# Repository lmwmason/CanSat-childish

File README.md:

# CanSat-childish

CanSat-childish is the open-source code and hardware for a two-tier CanSat
project by the Space Chamchu team: a **mother CanSat** that is dropped, steadies
itself with a reaction wheel, spins up, opens a door, ejects its wings and
glides back around the drop point, and small **child CanSats** that fall under a
parachute and record the descent. A **ground station** receives the mother's
telemetry over a TBS Crossfire link, shows it live and records it to CSV.

The repository holds every part of the system:

- **Mother firmware** — STM32F410RB. Fuses two IMUs, detects the drop, stabilizes
  and spins the body with a reaction wheel, opens the door, ejects the wings,
  flies the elevons (manual from the radio or automatic with GPS), detects the
  landing, and sends telemetry down the CRSF link.
- **Child firmware** — ATmega328 (Arduino Pro Mini). Reads barometer, IMU and
  humidity sensors, releases a parachute with a servo and logs the whole flight
  to EEPROM so it can be dumped over serial after landing.
- **Ground station** — a PyQt6 desktop app (Mission Planner style) that runs on a
  Raspberry Pi with a Crossfire Micro TX V2, or on a normal PC. Live flight view,
  ground track, CSV recording and the AUX switches of the mother.
- **KAIST kit ground station** — a second, independent ground station for the
  official KAIST CanSat kit. It runs as a small local web server and shows the
  flight and the wind field in two browser windows side by side.
- **Simulator** — the flight logic as a hardware-independent C core, run on a
  rigid-body physics engine, with a live 3D viewer.
- **PCB** — the KiCad project of the mother board.

## Mother mission

The mother's mission is a state machine on the STM32. Every number below is a
constant in the source and can be tuned.

1. **Drop detection** — the acceleration magnitude stays between 9.7 and
   9.9 m/s² for 300 ms **and** the AUX1 switch on the radio is on.
2. **2 s later** — the reaction wheel turns on and holds the current heading.
3. **Stable** (yaw rate under 8°/s and yaw error under 10° for 1 s) — the wheel
   spins the body up at full power.
4. **180°/s reached** — the servo opens the door.
5. **5 s at maximum speed**, then the wheel brakes and holds the heading again.
6. **Stable again** — the two wing servos eject the wings.
7. **Elevons** — the AUX2 switch selects manual (sticks) or automatic. Automatic
   mode levels the aircraft and circles around the point where the drop was
   detected (50 m radius) using the GPS.
8. **Landing** — motionless for 3 s (at least 10 s after the drop): the buzzer
   sounds and all LEDs blink.

## Tech stack

- **Mother firmware:** C, STM32 HAL, [STM32CubeMX](https://www.st.com/en/development-tools/stm32cubemx.html) project (`.ioc`) with IAR EWARM project files
- **Sensors on the mother:** MPU6050 + ICM-42688 (I2C), u-blox NEO-6M GPS (I2C / DDC), TBS Crossfire receiver (CRSF, UART)
- **Child firmware:** C++ / Arduino framework with [PlatformIO](https://platformio.org/); BMP280, MPU6050 (on-chip DMP), DHT11
- **Ground station:** Python 3, [PyQt6](https://www.riverbankcomputing.com/software/pyqt/) (Qt Serial Port), [PyInstaller](https://pyinstaller.org/) and AppImage for releases
- **KAIST kit ground station:** Python 3 (standard-library HTTP server, numpy, Pillow, pyserial), a plain HTML / canvas browser UI; `wind_field/` for the wind estimate
- **Simulator:** C11, [Open Dynamics Engine](https://www.ode.org/), Python with matplotlib / numpy for the viewer
- **Hardware design:** [KiCad](https://www.kicad.org/)

## Getting started

### Ground station

The easiest way is a build from the
[Releases](https://github.com/lmwmason/CanSat-childish/releases) page:

| File | For |
| ---- | --- |
| `CanSatGroundStation-aarch64.AppImage` | Raspberry Pi 4 / 5, 64-bit OS |
| `CanSatGroundStation-x86_64.AppImage` | Linux PC |
| `CanSatGroundStation-…-windows-x64.zip` | Windows PC |
| `CanSatGroundStation.pyz` + `run-on-pi.sh` | Any Raspberry Pi OS, if the AppImage does not work |

On a Raspberry Pi:

```bash
sudo apt install libfuse2 libxcb-cursor0
chmod +x CanSatGroundStation-aarch64.AppImage
./CanSatGroundStation-aarch64.AppImage
```

To run it from source:

```bash
cd guiTool
python3 -m venv .venv
.venv/bin/pip install -r requirements.txt
.venv/bin/python -m cansat_gui
```

Pick **Demo (synthetic flight)** in the Mother bar to try everything without
hardware. For the real link, choose the serial port and 400000 baud (CRSF). The
wiring between the Raspberry Pi and the Crossfire module is in
[`guiTool/pinmap.md`](./guiTool/pinmap.md). Telemetry is recorded to
`~/CanSat Logs/` (or `guiTool/logs/` when run from source).

Run the tests with `python -m unittest discover -s tests` inside `guiTool`.
To build a release locally:

```bash
pip install -r requirements-build.txt
pyinstaller cansat_gui.spec --noconfirm
tools/make_appimage.sh
```

Pushing a tag named `gui-vX.Y.Z` makes GitHub Actions
([`gui-release.yml`](./.github/workflows/gui-release.yml)) build the AppImages
for aarch64 and x86_64 and the Windows zip, and publish them as a release.

### KAIST kit ground station

A separate program from the one above, for the official KAIST CanSat kit (GPS,
IMU, ATLM / DTLM channels, camera). It needs Python 3 with numpy, Pillow and
pyserial, and a browser.

```bash
python3 -m venv kaist_ground_station/.venv
kaist_ground_station/.venv/bin/pip install -r kaist_ground_station/requirements.txt
./kaist_ground_station/run.sh
```

`run.sh` finds the USB serial adapter, connects at 115200 baud, dials the kit's
Bluetooth address from the config and opens two windows: the flight and control
page at `http://127.0.0.1:8765/` and the wind-field page at `/wind`. If no
adapter is found the UI still opens so a port can be picked by hand.

| Command | What it does |
| ------- | ------------ |
| `run.sh` / `run.sh live [PORT]` | Connect to the kit |
| `run.sh demo` | Replay the bundled example recording, no hardware needed |
| `run.sh replay FILE` | Replay a recorded `traffic.jsonl` |
| `run.sh mock` | Fake kit built from a real GoPro descent, for trying the UI |
| `run.sh headless` | Capture without a window |
| `run.sh test` | Run the unit tests |

Nothing is recorded until **Record** is pressed (or `auto_start` is set).
Checkpoints such as *Drop* or *Parachute open* are saved with the recording and
shown again in a replay. Language, colors, fonts, alarm limits, checkpoint
buttons, the Bluetooth address and the windows to open are all in
[`kaist_ground_station/config/ui.cfg`](./kaist_ground_station/config/ui.cfg).
Protocol notes and the hardware test steps are in
[`kaist_ground_station/`](./kaist_ground_station/).

### Mother firmware

1. Open `firmware/motherCansat-Firmware/motherCansat-Firmware.ioc` in
   STM32CubeMX to inspect or regenerate the peripheral setup.
2. Build and flash with your STM32 toolchain (the `EWARM` folder contains the IAR
   project). Keep your own code inside the `USER CODE` blocks of `main.c`.
3. Check the wiring against
   [`firmware/motherCansat-Firmware/pinmap.md`](./firmware/motherCansat-Firmware/pinmap.md).
   Several pins (wheel motor, servos, buzzer, LEDs) are not labeled in the `.ioc`,
   so the pin map is the reference.

The mission constants live in the headers of the modules, for example
`mission.h`, `drop_detect.h`, `landing_detect.h`, `elevon.h` and `nav.h`.

### Child firmware

```bash
cd firmware/childCansat-Firmware
pio run -t upload
pio device monitor -b 115200
```

The serial monitor accepts `s` (status), `d` (dump the flight log as CSV) and
`e` (erase the log).

### Simulator

Needs `gcc`, `make`, the ODE development package (`ode-devel` on Fedora,
`libode-dev` on Debian / Ubuntu) and Python with `matplotlib` and `numpy` for the
viewer.

```bash
cd simulator
./run.sh              # build, then an interactive menu
./run.sh mother       # the mothership simulation
./run.sh child 1      # a child satellite simulation (1 to 3)
./run.sh test         # the headless failsafe test
./run.sh viz          # live 3D telemetry viewer
./run.sh all          # mother + 3 children + viewer together
```

## Project structure

```
firmware/
  childCansat-Firmware/    PlatformIO project of the child CanSat
    src/                   main, boot, mission, sensors, storage (EEPROM log), comm, ui, core, config
    lib/                   bmp280, dht11 and mpu6050 drivers
    pinmap.md              Pin assignments of the child
  motherCansat-Firmware/   STM32CubeMX project of the mother CanSat
    Core/Src/              main.c and the application modules:
                             imu, gps, nav, crsf, drop, mission, reaction_wheel, pid,
                             door, wings, elevon, soft_pwm, wheel_motor, landing, indicator
    pinmap.md              Pin assignments of the mother
guiTool/
  cansat_gui/              The PyQt6 ground station (CRSF decoder, CSV logger, pages)
  tests/                   Frame-format tests against the real firmware output
  tools/                   Packaging scripts (AppImage, .pyz, Raspberry Pi launcher)
  pinmap.md                Wiring Raspberry Pi <-> Crossfire TX module
kaist_ground_station/      Ground station for the KAIST kit (web UI)
  web/                     HTTP server and the browser page
  config/                  ui.cfg (language, colors, alarms, checkpoints)
  demo/                    Bundled example recording for `run.sh demo`
  tools/                   Mock kit for trying the UI without hardware
wind_field/                 Wind estimate from GPS descents, used by the KAIST ground station
simulator/
  core/                    Hardware-independent flight logic in C
  sim/                     Mothership and child simulations (physics)
  viz/                     Live 3D viewer (Python)
pcb/
  motherBoard/kicad-pcb/   KiCad project of the mother board
photos/                    Schematic and PCB exports
.github/workflows/         Ground station release build
```

## Status

The mother firmware and the ground station are verified on a PC: the telemetry
frames the firmware produces are decoded correctly by the ground station, and the
mission logic was simulated. They have **not yet been tested end to end on the
real hardware**. The mother's pin assignments are chosen in `pinmap.md`, and the
Crossfire module pins should be checked before powering anything.

The KAIST kit ground station has received and recorded real flights from the kit
over its Bluetooth link. The kit sends GPS, IMU and ATLM about every 2 seconds
because its single transmit queue is shared with the camera image.

## License

Licensed under the [Apache License 2.0](./LICENSE).

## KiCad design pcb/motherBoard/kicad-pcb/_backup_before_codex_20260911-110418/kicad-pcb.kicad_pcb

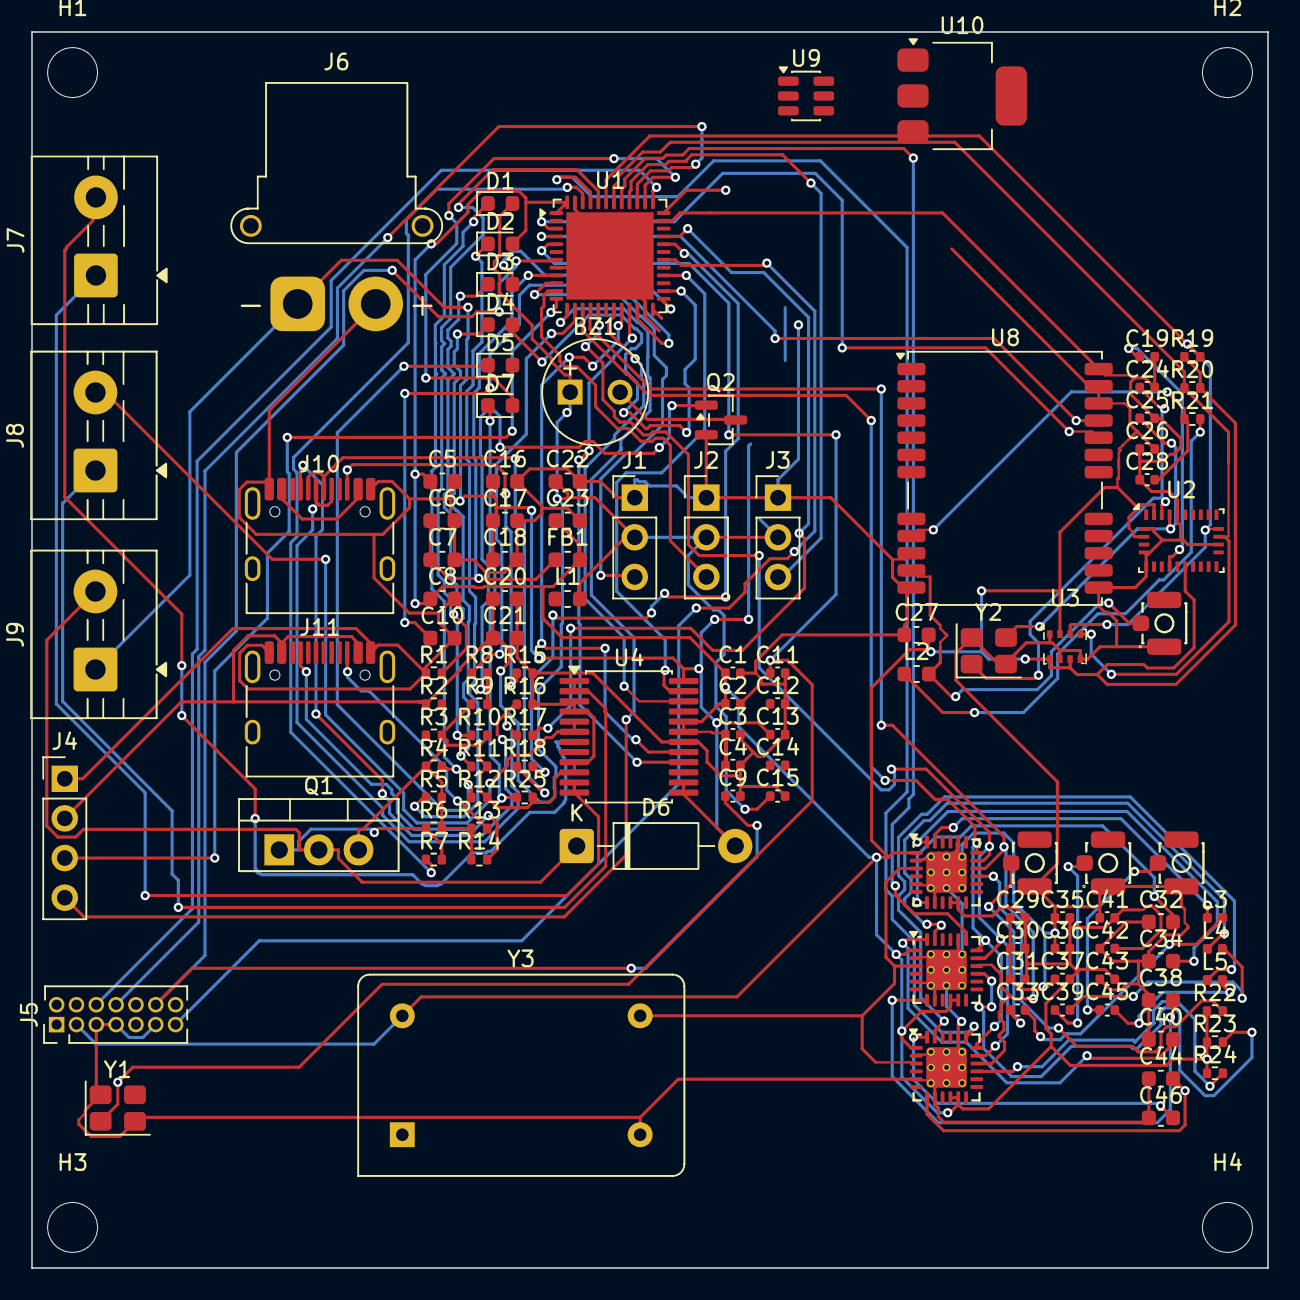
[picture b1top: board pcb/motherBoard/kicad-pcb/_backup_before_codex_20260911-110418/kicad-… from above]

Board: 2 copper layers, 79.2 x 79.2 mm, 119 parts (0 on the bottom side), 93 nets.

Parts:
BZ1: Buzzer; MagneticBuzzer_Kingstate_KCG0601
C1, C2, C3, C4, C9, C11, C12, C13, C14, C15, C19, C26, C29, C30, C31, C35, C36, C37, C41, C42, C43: 100n; C_0402_1005Metric
C5, C16, C17, C27: 10u; C_0603_1608Metric
C6: 10n; C_0603_1608Metric
C7, C8: 1u; C_0603_1608Metric
C10, C32, C34, C38, C40, C44, C46: 4.7u; C_0603_1608Metric
C18: 100u; C_0603_1608Metric
C20, C21, C22, C23: 22u; C_0603_1608Metric
C24, C25: 22p; C_0402_1005Metric
C28: 10n; C_0402_1005Metric
C33, C39, C45: 10p; C_0402_1005Metric
D1, D2: RED; LED_0603_1608Metric
D3: BLUE; LED_0603_1608Metric
D4: YELLOW; LED_0603_1608Metric
D5: ORANGE; LED_0603_1608Metric
D6: 1N4007; D_DO-41_SOD81_P10.16mm_Horizontal
D7: PINK; LED_0603_1608Metric
FB1: 120R; L_0603_1608Metric
H1, H2, H3, H4: MountingHole; MountingHole_3.2mm_M3
J1, J2, J3: SG90; PinHeader_1x03_P2.54mm_Vertical
J4: ELRS; PinHeader_1x04_P2.54mm_Vertical
J5: Conn_ST_STDC14; PinHeader_2x07_P1.27mm_Vertical
J6: 3s lipo xt30; AMASS_XT30PW-F_1x02_P2.50mm_Horizontal
J7: roll_DC; TerminalBlock_MaiXu_MX126-5.0-02P_1x02_P5.00mm
J8: pitch_DC; TerminalBlock_MaiXu_MX126-5.0-02P_1x02_P5.00mm
J9: solenoid_valve; TerminalBlock_MaiXu_MX126-5.0-02P_1x02_P5.00mm
J10: raspberrypi-serial; USB_C_Receptacle_HRO_TYPE-C-31-M-12
J11: raspberrypi-power; USB_C_Receptacle_HRO_TYPE-C-31-M-12
J12, J13, J14, J15: U.FL; IPEX-SMD_BWIPX-1-001E
L1: 4.7u; L_0603_1608Metric
L2: 47n; L_0603_1608Metric
L3, L4, L5: 27n; L_0402_1005Metric
Q1: IRLZ44N; TO-220-3_Vertical
Q2: 2N7002; SOT-23
R1, R6, R9, R22, R23, R24: 10k; R_0402_1005Metric
R2: 100k; R_0402_1005Metric
R3: 13.5k; R_0402_1005Metric
R4, R5, R10, R11, R12, R25: 1k5; R_0402_1005Metric
R7, R8: 100R; R_0402_1005Metric
R13, R14, R15, R16: 5k1; R_0402_1005Metric
R17, R18: 22R; R_0402_1005Metric
R19, R20: 4.7k; R_0402_1005Metric
R21: 10R; R_0402_1005Metric
U1: STM32F401CBU6; QFN-48-1EP_7x7mm_P0.5mm_EP5.6x5.6mm
U2: BNO055; LGA-28_5.2x3.8mm_P0.5mm
U3: BMP280; Bosch_LGA-8_2x2.5mm_P0.65mm_ClockwisePinNumbering
U4: TB6612FNG; SSOP-24_5.3x8.2mm_P0.65mm
U5, U6, U7: SX1262IMLTRT; QFN-24-1EP_4x4mm_P0.5mm_EP2.6x2.6mm_ThermalVias
U8: NEO-M8N; ublox_NEO
U9: TPS54302; SOT-23-6
U10: AMS1117-3.3; SOT-223-3_TabPin2
Y1: 16MHz; Crystal_SMD_3225-4Pin_3.2x2.5mm
Y2: 32.768kHz; Crystal_SMD_3225-4Pin_3.2x2.5mm
Y3: TCXO-14; Oscillator_DIP-14

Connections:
+3.3V: C1.1, C2.1, C3.1, C4.1, C5.1, C8.1, C23.1, C26.2, C27.2, C29.2, C30.2, C31.2, C35.2, C36.2, C37.2, C41.2, C42.2, C43.2, D2.2 (A), FB1.2, J5.3 (VCC), R19.1, R20.2, R22.1, R23.1, R24.1, U1.1 (VBAT), U1.24 (VDD), U1.36 (VDD), U1.48 (VDD), U2.3 (VDD), U2.11 (~RESET), U2.28 (VDDIO), U3.2 (CSB), U3.6 (VDDIO), U3.8 (VDD), U4.19 (STBY), U4.20 (VCC), U5.1 (VDD_IN), U5.10 (VBAT), U5.11 (VBAT_IO), U6.1 (VDD_IN), U6.10 (VBAT), U6.11 (VBAT_IO), U7.1 (VDD_IN), U7.10 (VBAT), U7.11 (VBAT_IO), U8.22 (V_BCKP), U8.23 (VCC), U10.2 (VO), Y3.14 (Vcc)
+3.3VA: C6.1, C7.1, FB1.1, U1.9 (VREF+)
+5V: BZ1.1 (+), C15.1, C20.1, C21.1, C22.1, D1.2 (A), J1.2, J2.2, J3.2, J4.2, J11.A4 (VBUS), J11.A9 (VBUS), J11.B4 (VBUS), J11.B9 (VBUS), L1.2, R2.1, U10.3 (VI)
+12V: C13.1, C16.1, C17.1, C18.1, D6.2 (A), J6.1, J9.1, U4.13 (VM2), U4.14 (VM3), U4.24 (VM1), U9.3 (VIN), U9.5 (EN)
/3.3v_LED_K: D2.1 (K), R5.1
/5v_LED_K: D1.1 (K), R4.2
/HSE_IN: C11.1, U1.5 (PH0), Y1.1
/HSE_OUT: C12.1, U1.6 (PH1), Y1.3
BLUE-LED: D3.2 (A), U1.25 (PB12)
ELRS-RX: J4.3, U1.12 (PA2)
ELRS-TX: J4.4, U1.13 (PA3)
GND: C1.2, C2.2, C3.2, C4.2, C5.2, C6.2, C7.2, C8.2, C9.2, C10.2, C11.2, C12.2, C13.2, C15.2, C16.2, C17.2, C18.2, C19.2, C20.2, C21.2, C22.2, C23.2, C24.2, C25.2, C26.1, C27.1, C28.1, C29.1, C30.1, C31.1, C32.1, C34.1, C35.1, C36.1, C37.1, C38.1, C40.1, C41.1, C42.1, C43.1, C44.1, C46.1, J1.1, J2.1, J3.1, J4.1, J5.5 (GND), J5.7 (GND), J5.11 (GNDDetect), J6.2, J10.A1 (GND), J10.A12 (GND), J10.B1 (GND), J10.B12 (GND), J11.A1 (GND), J11.A12 (GND), J11.B1 (GND), J11.B12 (GND), J12.2 (Ext), J13.2 (Ext), J14.2 (Ext), J15.2 (Ext), Q1.3 (S), Q2.2 (S), R1.1, R3.2, R4.1, R5.2, R6.2, R9.1, R10.2, R11.2, R12.2, R13.1, R14.1, R15.2, R16.2, R25.2, U1.8 (VSSA), U1.23 (VSS), U1.35 (VSS), U1.47 (VSS), U1.49 (VSS), U2.2 (GND), U2.5 (PS1), U2.6 (PS0), U2.17 (COM3), U2.25 (GNDIO), U3.1 (GND), U3.5 (SDO), U3.7 (GND), U4.3 (PGND1), U4.4 (PGND1), U4.9 (PGND2), U4.10 (PGND2), U4.18 (GND), U5.2 (GND), U5.5 (GND), U5.8 (GND), U5.20 (GND), U5.25 (GND), U6.2 (GND), U6.5 (GND), U6.8 (GND), U6.20 (GND), U6.25 (GND), U7.2 (GND), U7.5 (GND), U7.8 (GND), U7.20 (GND), U7.25 (GND), U8.10 (GND), U8.12 (GND), U8.13 (GND), U8.24 (GND), U9.1 (GND), U10.1 (GND), Y1.2 (G), Y1.4 (G), Y2.2 (G), Y2.4 (G), Y3.7 (GND)
GPS-rx: U1.4 (PC15), U8.21 (RXD/SPI_MOSI)
GPS-tx: U1.3 (PC14), U8.20 (TXD/SPI_MISO)
J10_VBUS_NC: J10.A4 (VBUS), J10.A9 (VBUS), J10.B4 (VBUS), J10.B9 (VBUS)
unnamed: BZ1.2 (-), Q2.3 (D)
unnamed: C33.2, L3.2
unnamed: C39.2, L4.2
unnamed: C45.2, L5.2
unnamed: D3.1 (K), R10.1
unnamed: D4.1 (K), R11.1
unnamed: D5.1 (K), R12.1
unnamed: D6.1 (K), J9.2, Q1.2 (D)
unnamed: D7.1 (K), R25.1
unnamed: J7.1, U4.11 (BO1), U4.12 (BO1)
unnamed: J7.2, U4.7 (BO2), U4.8 (BO2)
unnamed: J8.1, U4.1 (AO1), U4.2 (AO1)
unnamed: J8.2, U4.5 (AO2), U4.6 (AO2)
unnamed: J10.A5 (CC1), R16.1
unnamed: J10.B5 (CC2), R15.1
unnamed: J10.A6 (D+), J10.B6 (D+), R17.1
unnamed: J10.A7 (D-), J10.B7 (D-), R18.1
unnamed: J11.A5 (CC1), R14.2
unnamed: J11.B5 (CC2), R13.2
unnamed: J12.1 (In), L2.2, U8.11 (RF_IN)
unnamed: C33.1, J13.1 (In)
unnamed: C39.1, J14.1 (In)
unnamed: C45.1, J15.1 (In)
unnamed: L2.1, R21.2
unnamed: Q1.1 (G), R6.1, R7.2
unnamed: Q2.1 (G), R8.2, R9.2
unnamed: R1.2, U1.44 (BOOT0)
unnamed: C10.1, U1.22 (VCAP1)
unnamed: C19.1, U2.9 (CAP)
unnamed: C24.1, U2.27 (XIN32), Y2.1
unnamed: C25.1, U2.26 (XOUT32), Y2.3
unnamed: L3.1, U5.23 (RFO)
unnamed: C32.2, U5.7 (VREG)
unnamed: C34.2, U5.24 (VR_PA)
unnamed: R22.2, U5.15 (~RESET)
unnamed: L4.1, U6.23 (RFO)
unnamed: C38.2, U6.7 (VREG)
unnamed: C40.2, U6.24 (VR_PA)
unnamed: R23.2, U6.15 (~RESET)
unnamed: L5.1, U7.23 (RFO)
unnamed: C44.2, U7.7 (VREG)
unnamed: C46.2, U7.24 (VR_PA)
unnamed: R24.2, U7.15 (~RESET)
unnamed: C28.2, R21.1, U8.9 (VCC_RF)
unnamed: C14.1, U9.6 (BOOT)
unnamed: R2.2, R3.1, U9.4 (FB)
unnamed: C14.2, L1.1, U9.2 (SW)
ORANGE-LED: D5.2 (A), U1.27 (PB14)
PINK-LED: D7.2 (A), U1.38 (PA15)
SG90-1: J1.3, U1.10 (PA0)
SG90-2: J2.3, U1.11 (PA1)
SG90-3: J3.3, U1.40 (PB4)
TB-AIN1: U1.18 (PB0), U4.21 (AIN1)
TB-AIN2: U1.19 (PB1), U4.22 (AIN2)
TB-BIN1: U1.20 (PB2), U4.17 (BIN1)
TB-BIN2: U1.21 (PB10), U4.16 (BIN2)
TB-PWMA: U1.28 (PB15), U4.23 (PWMA)
TB-PWMB: U1.29 (PA8), U4.15 (PWMB)
TCXO-OUT: U5.3 (XTA), U6.3 (XTA), U7.3 (XTA), Y3.8 (OUT)
YELLOW-LED: D4.2 (A), U1.26 (PB13)
bz-sw: R8.1, U1.14 (PA4)
lora1-nss: U1.2 (PC13), U5.19 (NSS)
lora2-nss: U1.41 (PB5), U6.19 (NSS)
lora3-nss: U1.45 (PB8), U7.19 (NSS)
lora-miso: U1.16 (PA6), U5.16 (MISO), U6.16 (MISO), U7.16 (MISO)
lora-mosi: U1.17 (PA7), U5.17 (MOSI), U6.17 (MOSI), U7.17 (MOSI)
lora-sck: U1.15 (PA5), U5.18 (SCK), U6.18 (SCK), U7.18 (SCK)
rasp-dm: R18.2, U1.32 (PA11)
rasp-dp: R17.2, U1.33 (PA12)
sensor-scl: R20.1, U1.42 (PB6), U2.18 (COM2), U3.4 (SCK)
sensor-sda: R19.2, U1.43 (PB7), U2.19 (COM1), U3.3 (SDI)
stdc14-RX: J5.13 (VCP_RX), U1.30 (PA9)
stdc14-TX: J5.14 (VCP_TX), U1.31 (PA10)
stdc14-rst: C9.1, J5.12 (~RST), U1.7 (NRST)
stdc14-swclk: J5.6 (JCLK/SWCLK), U1.37 (PA14)
stdc14-swdio: J5.4 (JTMS/SWDIO), U1.34 (PA13)
stdc14-swo: J5.8 (JTDO/SWO), U1.39 (PB3)
valve-sw: R7.1, U1.46 (PB9)

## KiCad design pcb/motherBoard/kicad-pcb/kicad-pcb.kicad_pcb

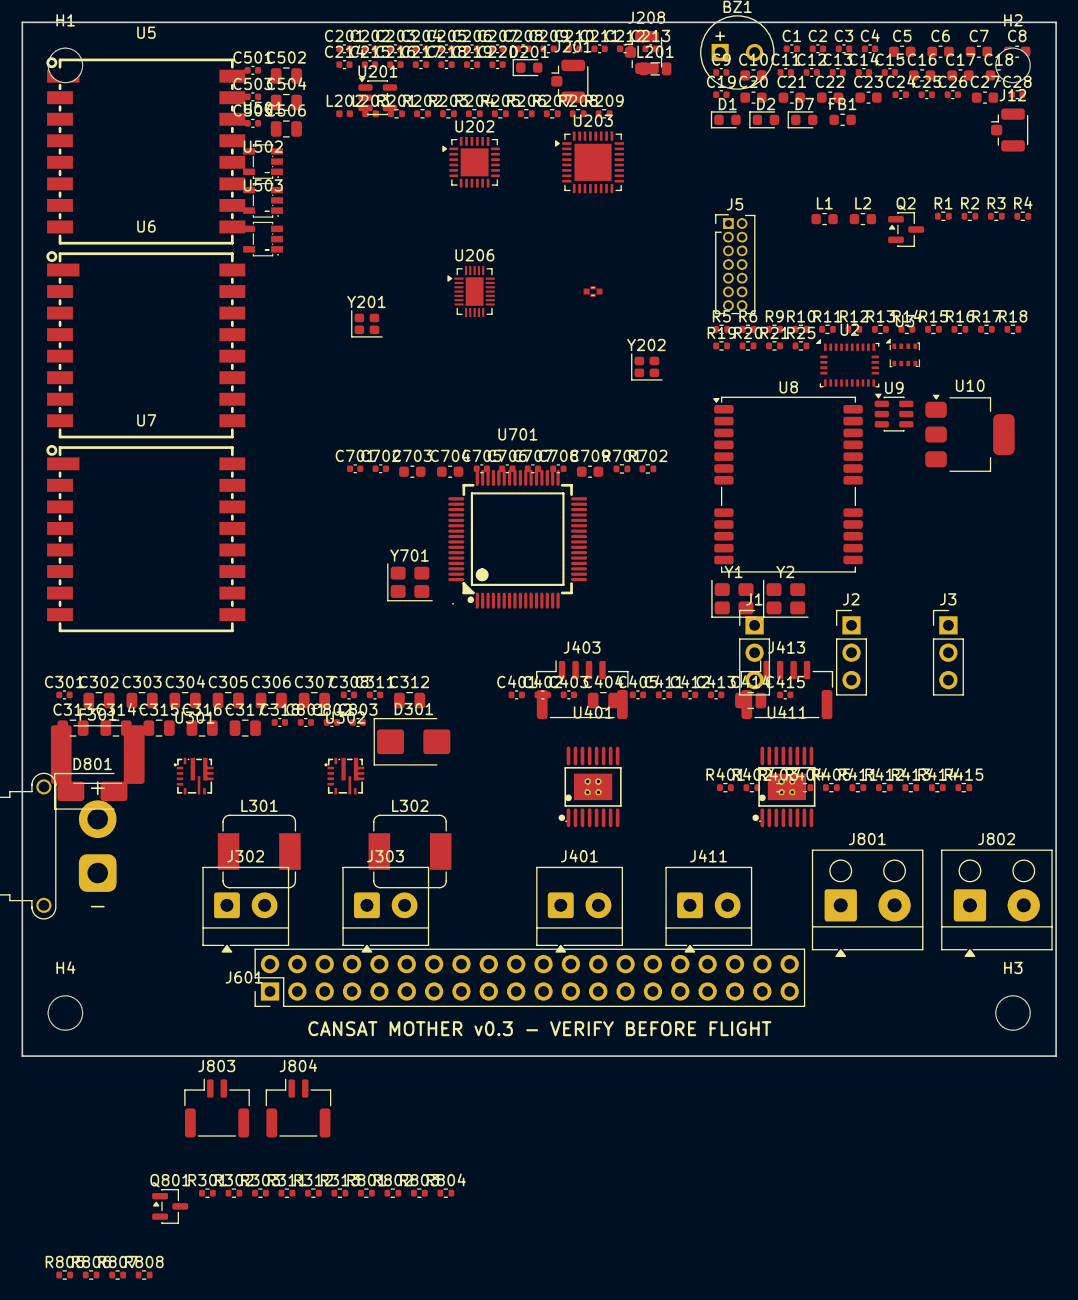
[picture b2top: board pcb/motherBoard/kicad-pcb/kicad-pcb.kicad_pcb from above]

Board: 4 copper layers, 96.0 x 96.0 mm, 214 parts (0 on the bottom side), 107 nets, no tracks yet.

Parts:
BZ1: Buzzer; MagneticBuzzer_Kingstate_KCG0601
C1, C2, C3, C4, C9, C13, C14, C15, C19, C26, C206, C207, C211, C218, C501, C503, C505, C705, C706, C707, C708: 100n; C_0402_1005Metric
C5, C16, C17, C27: 10u; C_0603_1608Metric
C6: 10n; C_0603_1608Metric
C7, C8: 1u; C_0603_1608Metric
C10, C709: 4.7u; C_0603_1608Metric
C11, C12: 12p; C_0402_1005Metric
C18: 100u; C_0603_1608Metric
C20, C21, C22, C23: 22u; C_0603_1608Metric
C24, C25: 22p; C_0402_1005Metric
C28, C203, C205, C405, C415: 10n; C_0402_1005Metric
C201: 1u; C_0402_1005Metric
C202: 2.2u; C_0402_1005Metric
C204: 470n, 10V; C_0402_1005Metric
C208, C209, C217, C219: 10p; C_0402_1005Metric
C210, C213: 1u 25v; C_0402_1005Metric
C212: 10u; C_0402_1005Metric
C214, C215, C216, C220: 1.2p; C_0402_1005Metric
C301, C311: 100n 25V; C_0402_1005Metric
C302, C303, C312, C313, C404, C414: 10u 25V C89831; C_0805_2012Metric
C304, C305, C306, C307, C314, C315, C316, C317: 22u 16V; C_0805_2012Metric
C308, C318: 100p C0G; C_0402_1005Metric
C401, C411: 22n 25V X7R; C_0402_1005Metric
C402, C412: 100n 16V X7R; C_0402_1005Metric
C403, C413: 100n 25V X7R; C_0402_1005Metric
C502, C504, C506: 10u; C_0805_2012Metric
C701, C702: 12p C1547; C_0402_1005Metric
C703, C704: 2.2u 10V; C_0603_1608Metric
C801: 100n 50V C1525; C_0402_1005Metric
C802, C803: 100n C1525; C_0402_1005Metric
D1, D2: RED; LED_0603_1608Metric
D7: PINK; LED_0603_1608Metric
D201: LED; LED_0603_1608Metric
D301: SMBJ18A; D_SMB
D801: SS34 C8678; D_SMA
F301: 10A resettable/polyfuse; Fuse_2920_7451Metric
FB1: 120R; L_0603_1608Metric
H1, H2, H3, H4: MountingHole; MountingHole_3.2mm_M3
J1, J2, J3: SG90; PinHeader_1x03_P2.54mm_Vertical
J5: Conn_ST_STDC14; PinHeader_2x07_P1.27mm_Vertical
J12: U.FL; U.FL_Hirose_U.FL-R-SMT-1_Vertical
J201, J208: Conn_Coaxial; U.FL_Hirose_U.FL-R-SMT-1_Vertical
J301: 3S_LIPO_INPUT; AMASS_XT30PW-F_1x02_P2.50mm_Horizontal
J302: PI5_5V1_OUT; TerminalBlock_4Ucon_1x02_P3.50mm_Horizontal
J303: SERVO_6V_OUT; TerminalBlock_4Ucon_1x02_P3.50mm_Horizontal
J401: REACTION_WHEEL_X; TerminalBlock_4Ucon_1x02_P3.50mm_Horizontal
J403: ENCODER_X; JST_GH_SM04B-GHS-TB_1x04-1MP_P1.25mm_Horizontal
J411: REACTION_WHEEL_Y; TerminalBlock_4Ucon_1x02_P3.50mm_Horizontal
J413: ENCODER_Y; JST_GH_SM04B-GHS-TB_1x04-1MP_P1.25mm_Horizontal
J601: RASPBERRY_PI_5_GPIO; PinHeader_2x20_P2.54mm_Vertical
J801: ARM KEY; Altech_AK100_1x02_P5.00mm
J802: 12V VALVE; Altech_AK100_1x02_P5.00mm
J803: DEPLOY SWITCH; JST_GH_SM02B-GHS-TB_1x02-1MP_P1.25mm_Horizontal
J804: RECOVERY INPUT; JST_GH_SM02B-GHS-TB_1x02-1MP_P1.25mm_Horizontal
L1: 4.7u; L_0603_1608Metric
L2: 47n; L_0603_1608Metric
L201: 15u; L_0805_2012Metric
L202, L203: 3n; L_0402_1005Metric
L301, L302: 3.3uH 12A C7461388; L_Sumida_CDMC6D28_7.25x6.5mm
Q2: 2N7002; SOT-23
Q801: AO3400A C20917; SOT-23
R1, R6, R9, R202, R207, R208, R209, R405, R415, R702: 10k; R_0402_1005Metric
R2, R201, R303, R313, R701: 100k; R_0402_1005Metric
R3: 13.5k; R_0402_1005Metric
R4, R5, R10, R11, R12, R25: 1k5; R_0402_1005Metric
R13, R14, R15, R16: 5k1; R_0402_1005Metric
R17, R18: 22R; R_0402_1005Metric
R19, R20: 4.7k; R_0402_1005Metric
R21: 10R; R_0402_1005Metric
R203: 2.2k; R_0402_1005Metric
R204: 1.2k; R_0402_1005Metric
R205: 3.3k; R_0402_1005Metric
R206: 12k; R_0402_1005Metric
R301: 75k 1%; R_0402_1005Metric
R302, R312: 10k 1%; R_0402_1005Metric
R311: 90k 1%; R_0402_1005Metric
R401, R411: 5.6k 1%; R_0402_1005Metric
R402, R412: 16k 1%; R_0402_1005Metric
R403, R413: 50k 1%; R_0402_1005Metric
R404, R414: 20k 1%; R_0402_1005Metric
R801, R805: 100k 1% C25741; R_0402_1005Metric
R802, R806: 27k 1% C25771; R_0402_1005Metric
R803: 100R C25076; R_0402_1005Metric
R804: 100k C25741; R_0402_1005Metric
R807, R808: 10k C25744; R_0402_1005Metric
U2: BNO055; LGA-28_5.2x3.8mm_P0.5mm
U3: BMP280; Bosch_LGA-8_2x2.5mm_P0.65mm_ClockwisePinNumbering
U5: Ra-01SH C2764087 CHILD_1; WIRELM-SMD_RA-01SH
U6: Ra-01SH C2764087 CHILD_2; WIRELM-SMD_RA-01SH
U7: Ra-01SH C2764087 CHILD_3; WIRELM-SMD_RA-01SH
U8: NEO-M8N; ublox_NEO
U9: TPS54302; SOT-23-6
U10: AMS1117-3.3; SOT-223-3_TabPin2
U201: 3V3. 500mA; TSOT-23-5
U202: SX1281; QFN-24-1EP_4x4mm_P0.5mm_EP2.6x2.6mm
U203: ESP8285; QFN-32-1EP_5x5mm_P0.5mm_EP3.45x3.45mm
U204: 2450FM07D0034T; 2450FM07D0034
U206: SE2431L; QFN-24-1EP_3x4mm_P0.4mm_EP1.65x2.65mm
U301: TPS56637RPAR (5.1V/6A); VQFN-HR-10_L3.0-W3.0_RPA
U302: TPS56637RPAR (6.0V/4A); VQFN-HR-10_L3.0-W3.0_RPA
U401, U411: DRV8874PWPR C1855818; HTSSOP-16_L5.0-W4.4-P0.65-LS6.4-BL-EP
U501, U502, U503: SN74LVC1G04DBVR C434067; SOT-23-5_L3.0-W1.7-P0.95-LS2.8-BR
U701: STM32F405RGT6 C15742; LQFP-64_L10.0-W10.0-P0.50-LS12.0-BL
Y1: 16MHz; Crystal_SMD_3225-4Pin_3.2x2.5mm
Y2: 32.768kHz; Crystal_SMD_3225-4Pin_3.2x2.5mm
Y201: 26M; Crystal_SMD_2016-4Pin_2.0x1.6mm
Y202: 52Mhz, 8pF; Crystal_SMD_2016-4Pin_2.0x1.6mm
Y701: 16MHz C13738; Crystal_SMD_3225-4Pin_3.2x2.5mm

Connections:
3.3v_LED_K: D2.1, R5.1
+3.3V: C1.1, C2.1, C3.1, C4.1, C5.1, C8.1, C23.1, C26.2, C27.2, C202.2, C206.2, C207.2, C211.2, C212.2, C213.1, C217.2, C218.1, C219.1, D2.2, FB1.2, J5.3, R19.1, R20.2, R202.2, R207.2, R209.1, U2.3, U2.11, U2.28, U3.2, U3.6, U3.8, U5.1, U6.1, U7.1, U8.22, U8.23, U10.2, U201.5, U202.11, U202.15, U203.1, U203.3, U203.4, U203.11, U203.17, U203.29, U203.30, U203.32, U206.19, U206.20, U206.21, U206.22
+3V3: C501.1, C502.1, C503.1, C504.1, C505.1, C506.1, C705.1, C706.1, C707.1, C708.1, C709.1, J403.1, J413.1, R402.1, R405.1, R412.1, R415.1, R702.1, R807.1, R808.1, U5.3, U6.3, U7.3, U501.5, U502.5, U503.5, U701.1, U701.13, U701.19, U701.32, U701.48, U701.64
+5V: BZ1.1, C15.1, C20.1, C21.1, C22.1, D1.2, L1.2, R2.1
+12V: C13.1, C16.1, C17.1, C18.1, U9.3, U9.5
ANT1: C214.1, L202.1, U206.15
ANT2: C215.1, L203.1, U206.13
ANT_SEL: U203.18, U206.16
ARM_SENSE: R805.2, R806.1, U701.3
BATTERY_SENSE: C801.1, R801.2, R802.1, U701.14
BAT_IN_PLUS: F301.1, J301.1
BOOT: R209.2, U203.15
BOOT0: R701.1, U701.60
BUSY: U202.7, U203.24
CS: R208.1, U202.19, U203.13
DEPLOY_SENSE: C802.1, J803.1, R807.2, U701.4
DIO: U202.8, U203.16
ENCODER_X_A: J403.3, U701.8
ENCODER_X_B: J403.4, U701.9
ENCODER_Y_A: J413.3, U701.10
ENCODER_Y_B: J413.4, U701.11
FRONTEND_IN: U204.3, U206.6
GND: C1.2, C2.2, C3.2, C4.2, C5.2, C6.2, C7.2, C8.2, C9.2, C10.2, C11.2, C12.2, C13.2, C15.2, C16.2, C17.2, C18.2, C19.2, C20.2, C21.2, C22.2, C23.2, C24.2, C25.2, C26.1, C27.1, C28.1, C201.1, C202.1, C203.1, C204.2, C205.1, C206.1, C207.1, C208.1, C209.1, C210.2, C211.1, C212.1, C213.2, C214.2, C215.2, C216.2, C217.1, C218.2, C219.2, C220.2, C302.2, C303.2, C304.2, C305.2, C306.2, C307.2, C312.2, C313.2, C314.2, C315.2, C316.2, C317.2, C403.2, C404.2, C405.2, C413.2, C414.2, C415.2, C501.2, C502.2, C503.2, C504.2, C505.2, C506.2, C701.2, C702.2, C703.2, C704.2, C705.2, C706.2, C707.2, C708.2, C709.2, C801.2, C802.2, C803.2, D201.1, D301.2, J1.1, J2.1, J3.1, J5.5, J5.7, J5.11, J12.2, J201.2, J208.2, J301.2, J302.2, J303.2, J403.2, J413.2, J601.6, J601.9, J601.14, J601.20, J601.25, J601.30, J601.34, J601.39, J803.2, J804.2, Q2.2, Q801.2, R1.1, R3.2, R4.1, R5.2, R6.2, R9.1, R10.2, R11.2, R12.2, R13.1, R14.1, R15.2, R16.2, R25.2, R201.2, R206.2, R208.2, R302.2, R312.2, R401.2, R403.2, R404.2, R411.2, R413.2, R414.2, R701.2, R802.2, R804.2, R806.2, U2.2, U2.5, U2.6, U2.17, U2.25, U3.1, U3.5, U3.7, U5.2, U5.8, U5.9, U5.16, U6.2, U6.8, U6.9, U6.16, U7.2, U7.8, U7.9, U7.16, U8.10, U8.12, U8.13, U8.24, U9.1, U10.1, U201.2, U202.5, U202.13, U202.20, U202.21, U202.23, U202.24, U202.25, U203.33, U204.2, U204.4, U206.9, U206.10, U206.11, U206.12, U206.14, U206.18, U206.25, U301.3, U301.9, U301.10, U302.3, U302.9, U302.10, U401.9, U401.15, U401.16, U401.17, U411.9, U411.15, U411.16, U411.17, U501.3, U502.3, U503.3, U701.12, U701.18, U701.63, Y1.2, Y1.4, Y2.2, Y2.4, Y201.2, Y201.4, Y202.2, Y202.4
GPS-rx: U8.21, U701.38
GPS-tx: U8.20, U701.37
HSE_IN: C701.1, U701.5, Y701.1
HSE_OUT: C702.1, U701.6, Y701.2
LORA1_BUSY: U5.10, U701.25
LORA1_DIO1: U5.6, U701.39
LORA1_NSS: U5.15, U701.24
LORA1_RFSW_RX: U5.11, U501.4
LORA1_RFSW_TX: U5.5, U5.7, U501.2
LORA2_BUSY: U6.10, U701.50
LORA2_DIO1: U6.6, U701.51
LORA2_NSS: U6.15, U701.40
LORA2_RFSW_RX: U6.11, U502.4
LORA2_RFSW_TX: U6.5, U6.7, U502.2
LORA3_BUSY: U7.10, U701.53
LORA3_DIO1: U7.6, U701.54
LORA3_NSS: U7.15, U701.52
LORA3_RFSW_RX: U7.11, U503.4
LORA3_RFSW_TX: U7.5, U7.7, U503.2
LORA_RESET_N: U5.4, U6.4, U7.4, U701.62
LORA_SPI_MISO: U5.13, U6.13, U7.13, U701.22
LORA_SPI_MOSI: U5.14, U6.14, U7.14, U701.23
LORA_SPI_SCK: U5.12, U6.12, U7.12, U701.21
MISO: U202.16, U203.10
MOSI: U202.17, U203.12
MOTOR_ENABLE: U401.3, U411.3, U701.33
MOTOR_X_CPH: C401.1, U401.13
MOTOR_X_CPL: C401.2, U401.14
MOTOR_X_CURRENT: C405.1, R401.1, U401.6, U701.15
MOTOR_X_DIR: U401.2, U701.56
MOTOR_X_FAULT_N: R405.2, U401.4, U701.34
MOTOR_X_IMODE: R404.1, U401.7
MOTOR_X_OUT1: J401.1, U401.8
MOTOR_X_OUT2: J401.2, U401.10
MOTOR_X_PWM: U401.1, U701.41
MOTOR_X_VCP: C402.1, U401.12
MOTOR_X_VREF: R402.2, R403.1, U401.5
MOTOR_Y_CPH: C411.1, U411.13
MOTOR_Y_CPL: C411.2, U411.14
MOTOR_Y_CURRENT: C415.1, R411.1, U411.6
MOTOR_Y_DIR: U411.2, U701.30
MOTOR_Y_FAULT_N: R415.2, U411.4, U701.35
MOTOR_Y_IMODE: R414.1, U411.7
MOTOR_Y_OUT1: J411.1, U411.8
MOTOR_Y_OUT2: J411.2, U411.10
MOTOR_Y_PWM: U411.1, U701.29
MOTOR_Y_VCP: C412.1, U411.12
MOTOR_Y_VREF: R412.2, R413.1, U411.5
PI5_5V1: C304.1, C305.1, C306.1, C307.1, C308.1, J302.1, J601.2, J601.4, L301.2, R301.1
PI5_BOOT: C301.1, U301.7
PI5_EN: R303.2, U301.1
PI5_FB: C308.2, R301.2, R302.1, U301.2
PI5_SW: C301.2, L301.1, U301.6
PI_UART_RX: J5.14, J601.8, U701.43
PI_UART_TX: J5.13, J601.10, U701.42
PWR_FLAG: C6.1, C7.1, FB1.1, U10.3
PWR_IN: C201.2, U201.1, U201.3
PWR_TXEN: R201.1, U203.19, U206.24
RADIO_OUT: U202.22, U204.1
RAW_BAT: C302.1, C303.1, C312.1, C313.1, C402.2, C403.1, C404.1, C412.2, C413.1, C414.1, D301.1, F301.2, J801.1, R303.1, R313.1, R801.1, U301.8, U302.8, U401.11, U411.11
RECOVERY_INPUT: C803.1, J804.1, R808.2, U701.57
RST: R207.1, U202.3, U203.14
SCK: U202.18, U203.9
SERVO_6V0: C314.1, C315.1, C316.1, C317.1, C318.1, J1.2, J2.2, J3.2, J303.1, L302.2, R311.1
SERVO_BOOT: C311.1, U302.7
SERVO_EN: R313.2, U302.1
SERVO_FB: C318.2, R311.2, R312.1, U302.2
SERVO_SW: C311.2, L302.1, U302.6
SG90-1: J1.3, U701.26
SG90-2: J2.3, U701.27
SG90-3: J3.3, U701.28
VALVE_ARMED: D801.1, J801.2, J802.1, R805.1
VALVE_GATE: Q801.1, R803.2, R804.1
VALVE_SW_NODE: D801.2, J802.2, Q801.3
VCAP1: C703.1, U701.31
VCAP2: C704.1, U701.47
V_DCC2: L201.2, U202.14
sensor-scl: R20.1, U2.18, U3.4, U701.58
sensor-sda: R19.2, U2.19, U3.3, U701.59
stdc14-rst: C9.1, J5.12, R702.2, U701.7
stdc14-swclk: J5.6, U701.49
stdc14-swdio: J5.4, U701.46
stdc14-swo: J5.8, U701.55
valve-sw: R803.1, U701.20

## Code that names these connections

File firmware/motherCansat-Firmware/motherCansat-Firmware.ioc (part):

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Mcu.Name=STM32F410R(8-B)Tx
Mcu.Package=LQFP64
Mcu.UserName=STM32F410RBTx
PA0-WKUP.Signal=S_TIM5_CH1
PA1.Signal=S_TIM5_CH2
PA10.Signal=S_TIM1_CH3
PA12.Signal=GPIO_Input
PA13.GPIOParameters=GPIO_Label
PA13.GPIO_Label=TMS
PA13.Mode=Serial_Wire
PA13.Signal=SYS_JTMS-SWDIO
PA14.GPIOParameters=GPIO_Label
PA14.GPIO_Label=TCK
PA14.Mode=Serial_Wire
PA14.Signal=SYS_JTCK-SWCLK
PA2.GPIOParameters=GPIO_Label
PA2.GPIO_Label=USART_TX
PA2.Mode=Asynchronous
PA2.Signal=USART2_TX
PA3.GPIOParameters=GPIO_Label
PA3.GPIO_Label=USART_RX
PA3.Mode=Asynchronous
PA3.Signal=USART2_RX
PA4.Signal=GPIO_Output
PA5.GPIOParameters=GPIO_Label
PA5.GPIO_Label=LD2 [Green Led]
PA5.Signal=GPIO_Output
PA8.Signal=S_TIM1_CH1
PA9.Signal=S_TIM1_CH2
PB12.Signal=GPIO_Output
PB13.Signal=GPIO_Output
PB14.Signal=GPIO_Output
PB15.Signal=GPIO_Output
PB3.GPIOParameters=GPIO_Label
PB3.GPIO_Label=SWO
PB3.Signal=SYS_JTDO-SWO
PB6.Mode=I2C
PB6.Signal=I2C1_SCL
PB7.Mode=I2C
PB7.Signal=I2C1_SDA
PC0.Signal=GPIO_Output
PC1.Signal=GPIO_Output
PC12.Signal=S_TIM11_CH1
PC13-ANTI_TAMP.GPIOParameters=GPIO_Label,GPIO_ModeDefaultEXTI
PC13-ANTI_TAMP.GPIO_Label=B1 [Blue PushButton]
PC13-ANTI_TAMP.GPIO_ModeDefaultEXTI=GPIO_MODE_IT_FALLING
PC13-ANTI_TAMP.Signal=GPXTI13
PC14-OSC32_IN.Mode=LSE-External-Oscillator
PC14-OSC32_IN.Signal=RCC_OSC32_IN
PC15-OSC32_OUT.Mode=LSE-External-Oscillator
PC15-OSC32_OUT.Signal=RCC_OSC32_OUT
PC2.Signal=GPIO_Output
PC3.Signal=GPIO_Output
PC4.Signal=GPIO_Output
PC5.Signal=GPIO_Analog
PC6.Mode=Asynchronous
PC6.Signal=USART6_TX
PC7.Mode=Asynchronous
PC7.Signal=USART6_RX
PC8.Signal=GPIO_Output
PC9.Signal=GPIO_Output
PH0\ -\ OSC_IN.Mode=HSE-External-Clock-Source
PH0\ -\ OSC_IN.Signal=RCC_OSC_IN
PH1\ -\ OSC_OUT.Mode=HSE-External-Clock-Source
PH1\ -\ OSC_OUT.Signal=RCC_OSC_OUT
RCC.HSE_VALUE=8000000
RCC.SYSCLKFreq_VALUE=84000000
RCC.SYSCLKSource=RCC_SYSCLKSOURCE_PLLCLK
board=NUCLEO-F410RB
boardIOC=true

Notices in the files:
README.md:
License: Apache 2.0
